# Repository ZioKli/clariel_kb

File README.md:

A custom split 3x5+3 keyboard. Based off the KLOR and Totem keyboards with a custom thumb section. Reversible PCB's, and support for Azoteq TPS65/TPS43 touchpads. THIS PROJECT IS IN EARLY DEVELOPMENT AND THE HARDWARE HAS NOT BEEN TESTED OR MANUFACTURED.

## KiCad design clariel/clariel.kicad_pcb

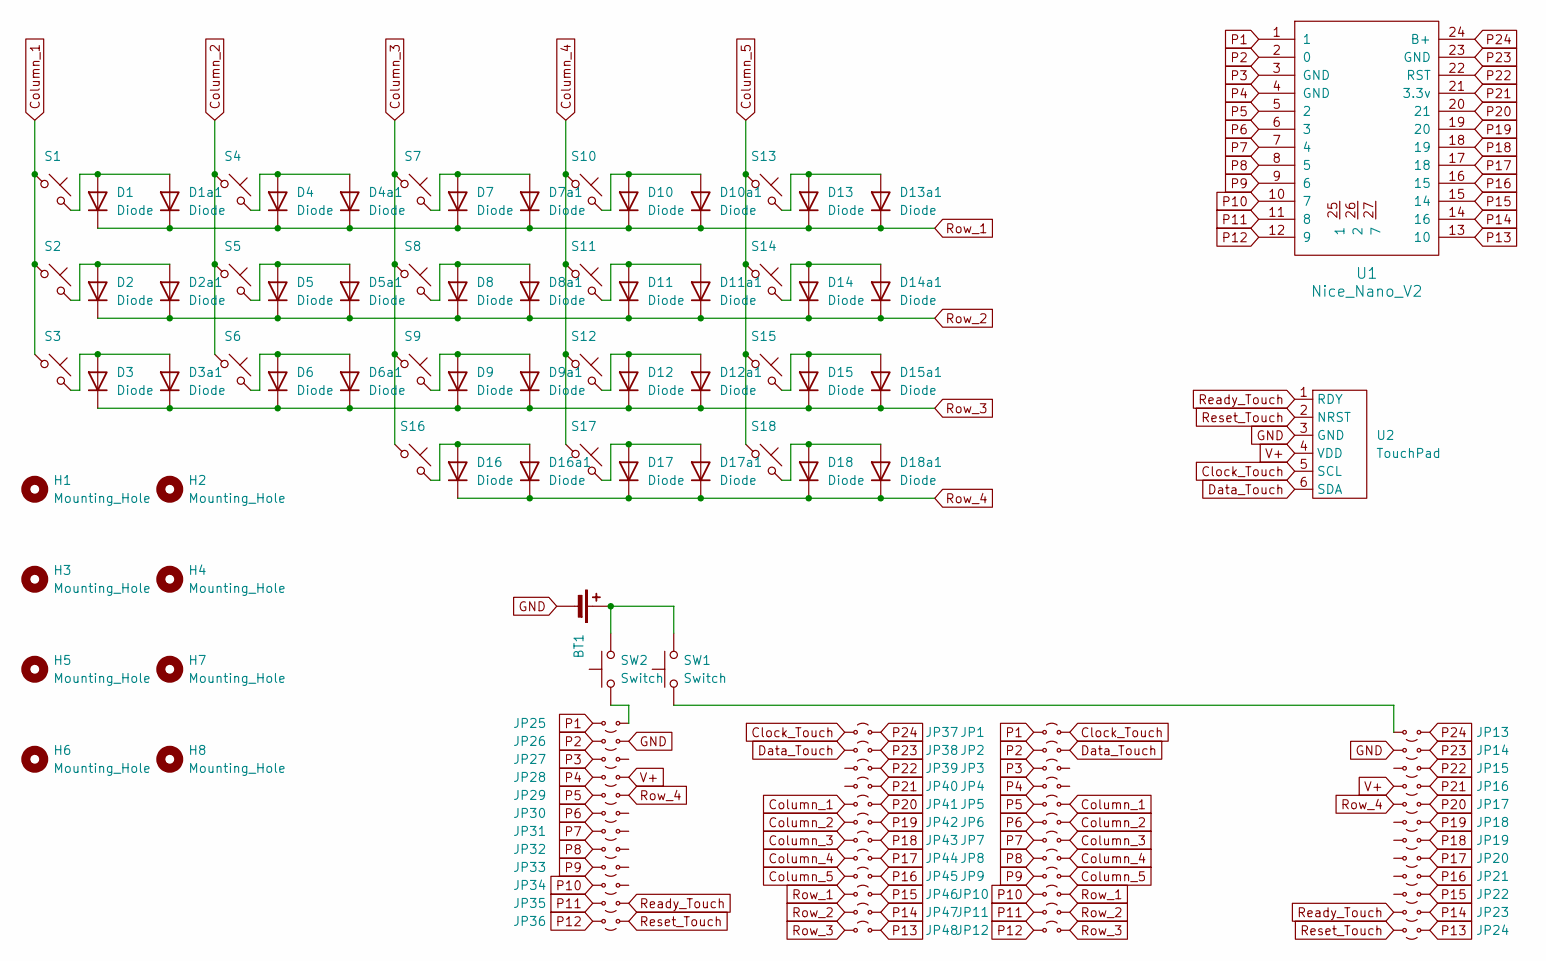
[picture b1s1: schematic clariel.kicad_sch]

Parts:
BT1: Battery
D1, D2, D3, D4, D5, D6, D7, D8, D9, D10, D11, D12, D13, D14, D15, D16, D17, D18: Diode; Diode_SOD-123
D1a1, D2a1, D3a1, D4a1, D5a1, D6a1, D7a1, D8a1, D9a1, D10a1, D11a1, D12a1, D13a1, D14a1, D15a1, D16a1, D17a1, D18a1: Diode; Diode_DO-35
H1, H2, H3, H4, H5, H6, H7, H8: Mounting_Hole; MountingHole_2.2mm_M2
JP1, JP2, JP3, JP4, JP5, JP6, JP7, JP8, JP9, JP10, JP11, JP12, JP13, JP14, JP15, JP16, JP17, JP18, JP19, JP20, JP21, JP22, JP23, JP24, JP25, JP26, JP27, JP28, JP29, JP30, JP31, JP32, JP33, JP34, JP35, JP36, JP37, JP38, JP39, JP40, JP41, JP42, JP43, JP44, JP45, JP46, JP47, JP48: Jumper_2_Small_Open; SolderJumper-2_P1.3mm_Open_TrianglePad1.0x1.5mm
S1, S2, S3, S4, S5, S6, S7, S8, S9, S10, S11, S12, S13, S14, S15, S16, S17, S18: Keyswitch; Choc_Hotswap
SW1, SW2: Switch; SW_SPDT_PCM12
U1: Nice_Nano_V2
U2: TouchPad; PinSocket_1x06_P1.00mm_Vertical

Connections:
Clock_Touch: JP1.2 (B), JP37.2 (B), U2.5 (SCL)
Column_1: JP5.2 (B), JP41.2 (B), S1.1, S2.1, S3.1
Column_2: JP6.2 (B), JP42.2 (B), S4.1, S5.1, S6.1
Column_3: JP7.2 (B), JP43.2 (B), S7.1, S8.1, S9.1, S16.1
Column_4: JP8.2 (B), JP44.2 (B), S10.1, S11.1, S12.1, S17.1
Column_5: JP9.2 (B), JP45.2 (B), S13.1, S14.1, S15.1, S18.1
Data_Touch: JP2.2 (B), JP38.2 (B), U2.6 (SDA)
GND: BT1.2 (-), JP14.2 (B), JP26.2 (B), U2.3 (GND)
unnamed: BT1.1 (+), SW1.2, SW2.2
unnamed 9: D1.2 (A), D1a1.2 (A), S1.2; also elsewhere on the board
unnamed 10: D2.2 (A), D2a1.2 (A), S2.2; also elsewhere on the board
unnamed 11: D3.2 (A), D3a1.2 (A), S3.2; also elsewhere on the board
unnamed 12: D4.2 (A), D4a1.2 (A), S4.2; also elsewhere on the board
unnamed 13: D5.2 (A), D5a1.2 (A), S5.2; also elsewhere on the board
unnamed 14: D6.2 (A), D6a1.2 (A), S6.2; also elsewhere on the board
unnamed 15: D7.2 (A), D7a1.2 (A), S7.2; also elsewhere on the board
unnamed 16: D8.2 (A), D8a1.2 (A), S8.2; also elsewhere on the board
unnamed 17: D9.2 (A), D9a1.2 (A), S9.2; also elsewhere on the board
unnamed 18: D10.2 (A), D10a1.2 (A), S10.2; also elsewhere on the board
unnamed 19: D11.2 (A), D11a1.2 (A), S11.2; also elsewhere on the board
unnamed 20: D12.2 (A), D12a1.2 (A), S12.2; also elsewhere on the board
unnamed 21: D13.2 (A), D13a1.2 (A), S13.2; also elsewhere on the board
unnamed 22: D14.2 (A), D14a1.2 (A), S14.2; also elsewhere on the board
unnamed 23: D15.2 (A), D15a1.2 (A), S15.2; also elsewhere on the board
unnamed 24: D16.2 (A), D16a1.2 (A), S16.2; also elsewhere on the board
unnamed 25: D17.2 (A), D17a1.2 (A), S17.2; also elsewhere on the board
unnamed 26: D18.2 (A), D18a1.2 (A), S18.2; also elsewhere on the board
unnamed: JP13.2 (B), SW1.1
unnamed: JP25.2 (B), SW2.1
P1: JP1.1 (A), JP25.1 (A), U1.1
P2: JP2.1 (A), JP26.1 (A), U1.2 (0)
P3: JP3.1 (A), JP27.1 (A), U1.3 (GND)
P4: JP4.1 (A), JP28.1 (A), U1.4 (GND)
P5: JP5.1 (A), JP29.1 (A), U1.5 (2)
P6: JP6.1 (A), JP30.1 (A), U1.6 (3)
P7: JP7.1 (A), JP31.1 (A), U1.7 (4)
P8: JP8.1 (A), JP32.1 (A), U1.8 (5)
P9: JP9.1 (A), JP33.1 (A), U1.9 (6)
P10: JP10.1 (A), JP34.1 (A), U1.10 (7)
P11: JP11.1 (A), JP35.1 (A), U1.11 (8)
P12: JP12.1 (A), JP36.1 (A), U1.12 (9)
P13: JP24.1 (A), JP48.1 (A), U1.13 (10)
P14: JP23.1 (A), JP47.1 (A), U1.14 (16)
P15: JP22.1 (A), JP46.1 (A), U1.15 (14)
P16: JP21.1 (A), JP45.1 (A), U1.16 (15)
P17: JP20.1 (A), JP44.1 (A), U1.17 (18)
P18: JP19.1 (A), JP43.1 (A), U1.18 (19)
P19: JP18.1 (A), JP42.1 (A), U1.19 (20)
P20: JP17.1 (A), JP41.1 (A), U1.20 (21)
P21: JP16.1 (A), JP40.1 (A), U1.21 (3.3v)
P22: JP15.1 (A), JP39.1 (A), U1.22 (RST)
P23: JP14.1 (A), JP38.1 (A), U1.23 (GND)
P24: JP13.1 (A), JP37.1 (A), U1.24 (B+)
Ready_Touch: JP23.2 (B), JP35.2 (B), U2.1 (RDY)
Reset_Touch: JP24.2 (B), JP36.2 (B), U2.2 (NRST)
Row_1: D1.1 (K), D1a1.1 (K), D4.1 (K), D4a1.1 (K), D7.1 (K), D7a1.1 (K), D10.1 (K), D10a1.1 (K), D13.1 (K), D13a1.1 (K), JP10.2 (B), JP46.2 (B); also elsewhere on the board
Row_2: D2.1 (K), D2a1.1 (K), D5.1 (K), D5a1.1 (K), D8.1 (K), D8a1.1 (K), D11.1 (K), D11a1.1 (K), D14.1 (K), D14a1.1 (K), JP11.2 (B), JP47.2 (B); also elsewhere on the board
Row_3: D3.1 (K), D3a1.1 (K), D6.1 (K), D6a1.1 (K), D9.1 (K), D9a1.1 (K), D12.1 (K), D12a1.1 (K), D15.1 (K), D15a1.1 (K), JP12.2 (B), JP48.2 (B); also elsewhere on the board
Row_4: D16.1 (K), D16a1.1 (K), D17.1 (K), D17a1.1 (K), D18.1 (K), D18a1.1 (K), JP17.2 (B), JP29.2 (B); also elsewhere on the board
V+: JP16.2 (B), JP28.2 (B), U2.4 (VDD)

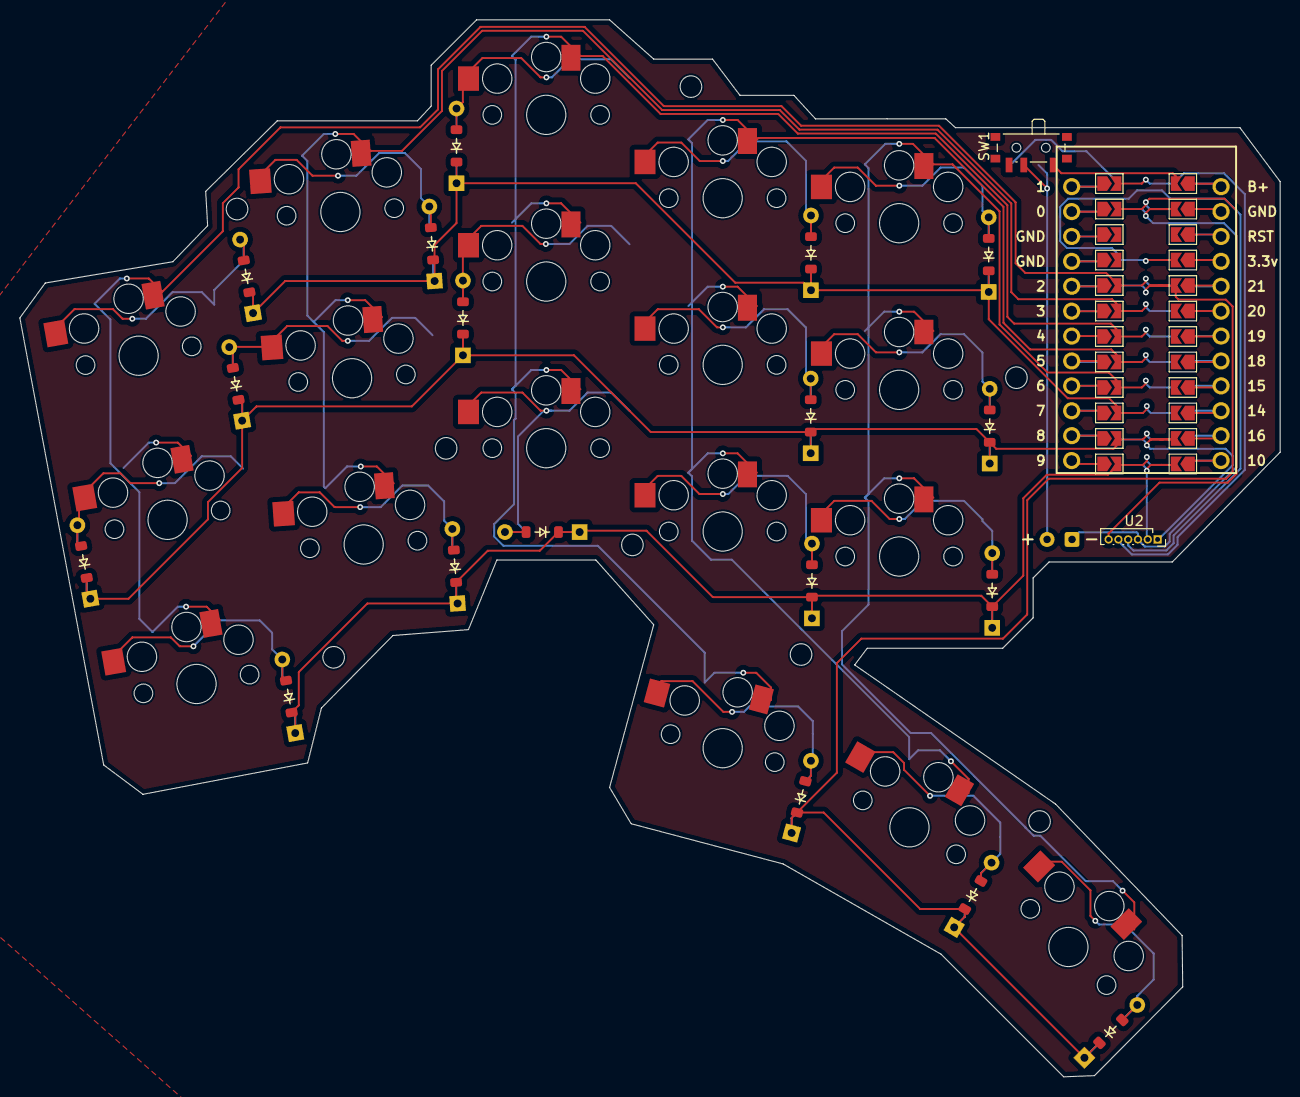
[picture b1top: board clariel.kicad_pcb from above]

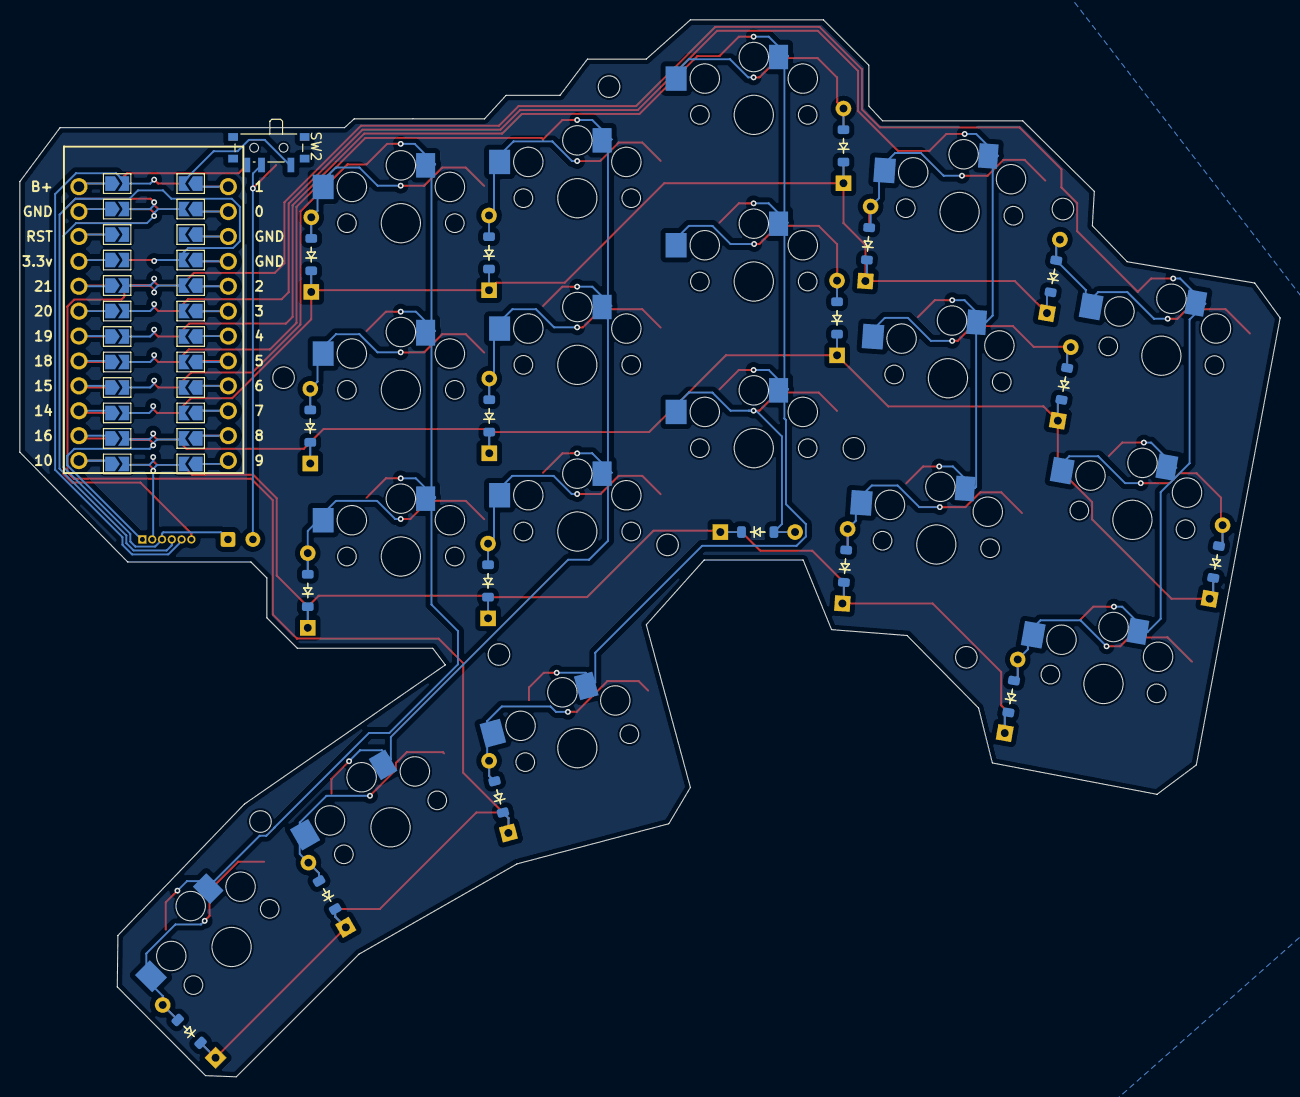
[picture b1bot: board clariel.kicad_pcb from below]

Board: 2 copper layers, 128.6 x 107.8 mm, 133 parts (78 on the bottom side), 60 nets.

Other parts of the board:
D1#2, D2#2, D3#2, D4#2, D5#2, D6#2, D7#2, D8#2, D9#2, D10#2, D11#2, D12#2, D13#2, D14#2, D15#2, D16#2, D17#2, D18#2: Diode; Diode_SOD-123

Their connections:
unnamed 9: D1#2.2 (A); also elsewhere on the board
unnamed 10: D2#2.2 (A); also elsewhere on the board
unnamed 11: D3#2.2 (A); also elsewhere on the board
unnamed 12: D4#2.2 (A); also elsewhere on the board
unnamed 13: D5#2.2 (A); also elsewhere on the board
unnamed 14: D6#2.2 (A); also elsewhere on the board
unnamed 15: D7#2.2 (A); also elsewhere on the board
unnamed 16: D8#2.2 (A); also elsewhere on the board
unnamed 17: D9#2.2 (A); also elsewhere on the board
unnamed 18: D10#2.2 (A); also elsewhere on the board
unnamed 19: D11#2.2 (A); also elsewhere on the board
unnamed 20: D12#2.2 (A); also elsewhere on the board
unnamed 21: D13#2.2 (A); also elsewhere on the board
unnamed 22: D14#2.2 (A); also elsewhere on the board
unnamed 23: D15#2.2 (A); also elsewhere on the board
unnamed 24: D16#2.2 (A); also elsewhere on the board
unnamed 25: D17#2.2 (A); also elsewhere on the board
unnamed 26: D18#2.2 (A); also elsewhere on the board
Row_1: D1#2.1 (K), D4#2.1 (K), D7#2.1 (K), D10#2.1 (K), D13#2.1 (K); also elsewhere on the board
Row_2: D2#2.1 (K), D5#2.1 (K), D8#2.1 (K), D11#2.1 (K), D14#2.1 (K); also elsewhere on the board
Row_3: D3#2.1 (K), D6#2.1 (K), D9#2.1 (K), D12#2.1 (K), D15#2.1 (K); also elsewhere on the board
Row_4: D16#2.1 (K), D17#2.1 (K), D18#2.1 (K); also elsewhere on the board

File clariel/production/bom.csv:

Designator,Footprint,Quantity,Value,LCSC Part #
BT1,Battery,1,Battery,
"D1_2, D1, D10_2, D10, D11_2, D11, D12_2, D12, D13_2, D13, D14_2, D14, D15_2, D15, D16_2, D16, D17_2, D17, D18_2, D18, D2_2, D2, D3_2, D3, D4_2, D4, D5_2, D5, D6_2, D6, D7_2, D7, D8_2, D8, D9_2, D9",Diode_SOD-123,36,Diode,
"D10A1, D11A1, D12A1, D13A1, D14A1, D15A1, D16A1, D17A1, D18A1, D1A1, D2A1, D3A1, D4A1, D5A1, D6A1, D7A1, D8A1, D9A1",Diode_DO-35,18,Diode,
"H1, H2, H3, H4, H5, H6, H7, H8",MountingHole_2.2mm_M2,8,Mounting_Hole,
"JP1, JP10, JP11, JP12, JP13, JP14, JP15, JP16, JP17, JP18, JP19, JP2, JP20, JP21, JP22, JP23, JP24, JP25, JP26, JP27, JP28, JP29, JP3, JP30, JP31, JP32, JP33, JP34, JP35, JP36, JP37, JP38, JP39, JP4, JP40, JP41, JP42, JP43, JP44, JP45, JP46, JP47, JP48, JP5, JP6, JP7, JP8, JP9",SolderJumper-2_P1.3mm_Open_TrianglePad1.0x1.5mm,48,Jumper_2_Small_Open,
"S1, S10, S11, S12, S13, S14, S15, S16, S17, S18, S2, S3, S4, S5, S6, S7, S8, S9",Choc_Hotswap,18,Keyswitch,
"SW1, SW2",SW_SPDT_PCM12,2,Switch,
U1,Nice_Nano_V2,1,Nice_Nano_V2,
U2,PinSocket_1x06_P1.00mm_Vertical,1,TouchPad,

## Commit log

2025-08-19 added ergogen layout
2025-08-22 first draft complete
2025-08-22 Create LICENSE
